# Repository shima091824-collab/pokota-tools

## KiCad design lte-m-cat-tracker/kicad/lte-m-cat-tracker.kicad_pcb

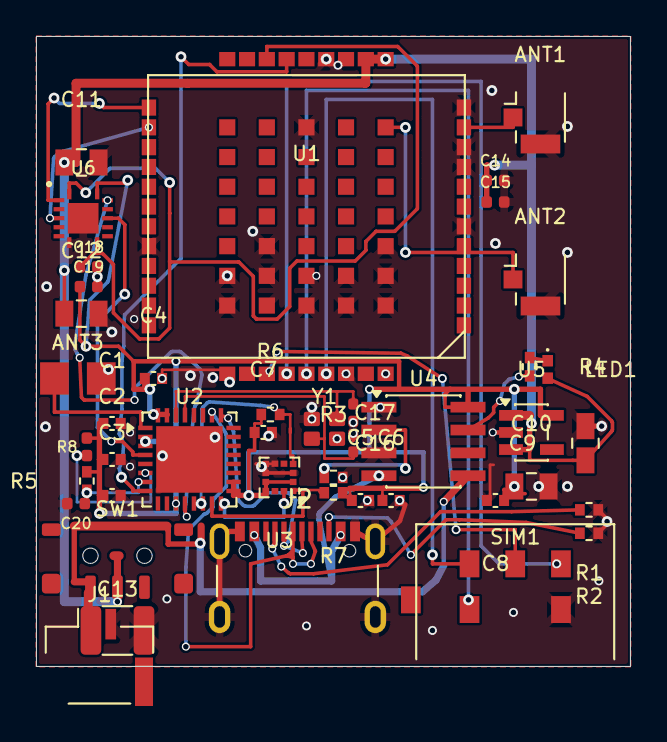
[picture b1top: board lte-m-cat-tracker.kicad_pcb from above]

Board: 2 copper layers, 33.0 x 35.0 mm, 43 parts (0 on the bottom side), 32 nets.

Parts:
ANT1: U.FL-LTE
ANT2: U.FL-GNSS
ANT3: RFANT3216120A5T; ChipAntenna_1206
C1, C2, C3, C4, C5, C6, C7, C8: 100nF
C9, C10, C11, C12: 10uF
C13: 100uF_6.3V_PolymerAl; C_1210_3225Metric
C14, C15, C18, C19, C20: 100nF; C_0402
C16, C17: 18pF
J1: JST-GH-1.25mm-2P
J2: TYPE-C-16PIN-2MD(073); USBC_16P_2MD073_C2765186
LED1: RED
R1, R2: 5.1k
R3: 3.3k
R4: 1k
R5: 10k
R6, R7: 4.7k
R8: 10k; C_0402
SIM1: SMN-305
SW1: MSK12C02-HB
U1: SIM7080G-M
U2: ESP32-C3
U3: LIS2DW12TR
U4: TP4056
U5: XC6220B331MR-G
U6: TXB0104RGYR; TXB0104_RGY14
Y1: 7D040000M01 40MHz 12pF

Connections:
+3.3V: C1.1, C2.1, C3.1, C4.1, C5.1, C6.1, C7.1, C8.1, C10.1, C19.1, R5.2, R6.1, R7.1, R8.2, U2.2, U2.3, U2.11, U2.17, U2.18, U2.31, U2.32, U3.2, U3.9, U3.10, U4.8, U5.5, U6.14
ACCEL_INT1: U2.16, U3.12
CC1: J2.A5, R1.2
CC2: J2.B5, R2.2
CHIP_EN: C20.1, R5.1, U2.7
CHRG: R4.2, U4.7
ESP_GPIO2: R8.1, U2.6
GND: ANT1.2, ANT2.2, ANT3.2, C1.2, C2.2, C3.2, C4.2, C5.2, C6.2, C7.2, C8.2, C9.2, C10.2, C11.2, C12.2, C13.2, C14.2, C15.2, C16.1, C17.2, C18.2, C19.2, C20.2, J1.2, J2.A1, J2.B1, J2.S, R1.1, R2.1, R3.2, SIM1.5, U1.8, U1.13, U1.19, U1.21, U1.27, U1.30, U1.31, U1.33, U1.36, U1.37, U1.45, U1.63, U1.66, U1.67, U1.69, U1.70, U1.71, U1.72, U1.73, U1.74, U1.75, U1.76, U1.77, U2.33, U3.3, U3.6, U3.7, U3.8, U4.1, U4.3, U5.2, U6.7, U6.15, Y1.2, Y1.4
GNSS_ANT: ANT2.1, U1.68
I2C_SCL: R7.2, U2.15, U3.1
I2C_SDA: R6.2, U2.14, U3.4
LED_ANODE: LED1.1, R4.1
LTE_ANT: ANT1.1, U1.32
PROG: R3.1, U4.2
SIM_CLK: SIM1.3, U1.16
SIM_DATA: SIM1.2, U1.15
SIM_PWRKEY: U1.39, U2.8
SIM_RST: SIM1.4, U1.17
SIM_RXD: U1.2, U6.4
SIM_RXD_33: U2.4, U6.11
SIM_TXD: U1.1, U6.2
SIM_TXD_33: U2.12, U6.13
SIM_VDD: SIM1.1, U1.18
USB_DN: J2.A7, J2.B7, U2.25
USB_DP: J2.A6, J2.B6, U2.26
VBAT: C13.1, J1.1, SW1.1, U4.5
VBAT_SW: C9.1, C11.1, C12.1, C14.1, C15.1, LED1.2, SW1.2, U1.34, U1.35, U5.1, U5.3
VDD_EXT: C18.1, U1.40, U6.1, U6.8
VUSB: J2.A4, J2.B4, U4.4
WIFI_ANT: ANT3.1, U2.1
XTAL_N: C16.2, U2.29, Y1.1
XTAL_P: C17.1, U2.30, Y1.3

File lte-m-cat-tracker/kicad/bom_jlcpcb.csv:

Comment,Designator,Footprint,LCSC Part #
SIM7080G-M,U1,SIM7080GM_LCC77,C18548266
ESP32-C3FH4,U2,QFN-32_5x5mm,C2858491
LIS2DW12TR,U3,LGA-12_2x2mm,C189624
TP4056,U4,SOIC-8,C16581
XC6220B331MR-G,U5,SOT-25,C86534
100nF 0402,C1 C2 C3 C4 C5 C6 C7 C8 C14 C15 C18 C19 C20,0402,C14663
10uF 0805,C9 C10 C11 C12,0805,C15850
100uF 6.3V X5R 1210,C13,1210,C49326798
5.1k 0402,R1 R2,0402,C23186
3.3k 0402,R3,0402,C22978
1k 0402,R4,0402,C21190
10k 0402,R5 R8,0402,C17414
4.7k 0402,R6 R7,0402,C23162
U.FL-R-SMT,ANT1 ANT2,U.FL_SMD,C317592
RFANT3216120A5T,ANT3,ChipAntenna_1206,C127629
SMN-305,SIM1,SIM_SMN-305,C266890
JST-PH-2mm-2P,J1,JST-PH-2P_SMD,C295747
USB-C-16P,J2,USB_C_16P_SMD,C2765186
MSK12C02,SW1,SW_MSK12C02,C431541
RED LED 0402,LED1,0402,C2286
7D040000M01 40MHz,Y1,XTAL_2016_4P,C648974
18pF 0402,C16 C17,0402,C1555
TXB0104RGYR,U6,TXB0104_RGY14,C400708

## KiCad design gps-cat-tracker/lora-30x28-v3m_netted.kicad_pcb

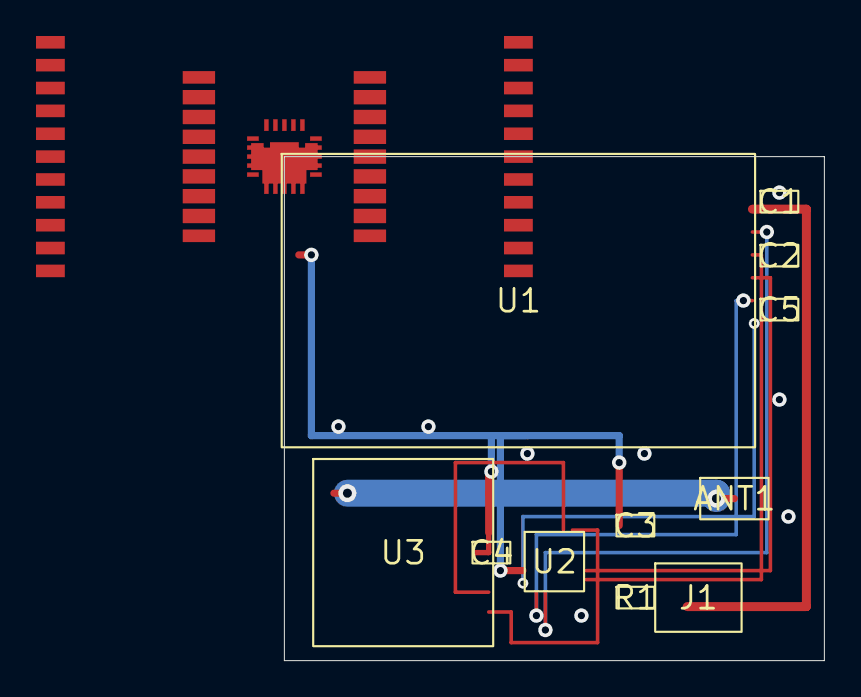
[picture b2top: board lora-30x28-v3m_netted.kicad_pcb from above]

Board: 2 copper layers, 30.0 x 28.0 mm, 11 parts (0 on the bottom side), 9 nets.

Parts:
ANT1: U.FL-R-SMT_IPEX
C1, C2, C3, C4: 100nF
C5: 1uF
J1: JST-GH_1.25mm_2P
R1: 10k
U1: E220-900T22S(JP)
U2: ATtiny3226-MFR_VQFN20
U3: MAX-M8Q-00B_LCC18

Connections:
AUX: U1.9, U2.7
M0: U1.5, U2.5
M1: ANT1.G2, C2.1, C5.1, U1.6, U1.8, U2.6, U2.11
Net-011: ANT1.G1, ANT1.S
Net-020: C1.1, J1.1, J1.2, U1.10
Net-026: C3.1, C4.1, U2.4, U3.4, U3.5, U3.6, U3.7, U3.8, U3.9
Net-037: U1.7, U2.12
UART1_RX: U2.17, U3.3
UART1_TX: U2.16, U3.2

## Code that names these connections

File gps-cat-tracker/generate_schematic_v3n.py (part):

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
def sym_e220():
    """E220-900T22S(JP) LoRa 920MHz module (hand solder, 22-pin)
    Right-side key pins (top→bottom): GND,TXD,RXD,AUX,M0,M1,pad7,pad8,GND,VCC,GND
    Left-side: GND/shield
    VDD3V3 = 3.3V output from internal LDO (powers MCU and GPS)
    """
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
def sym_tp4056():
    """TP4056 LiPo charger IC, ESOP-8
    Pin1=PROG, Pin2=GND, Pin3=GND, Pin4=VIN(VBUS)
    Pin5=CE(charge enable→VIN), Pin6=CHRG(OD,active-low), Pin7=STDBY(OD,active-low), Pin8=BAT
    Charge current = 1000/RPROG mA → R2=5kΩ → 200mA
    """
    return """    (symbol "Custom:TP4056"
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
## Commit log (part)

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2026-05-07 初回アップロード
2026-05-07 gitignore更新
